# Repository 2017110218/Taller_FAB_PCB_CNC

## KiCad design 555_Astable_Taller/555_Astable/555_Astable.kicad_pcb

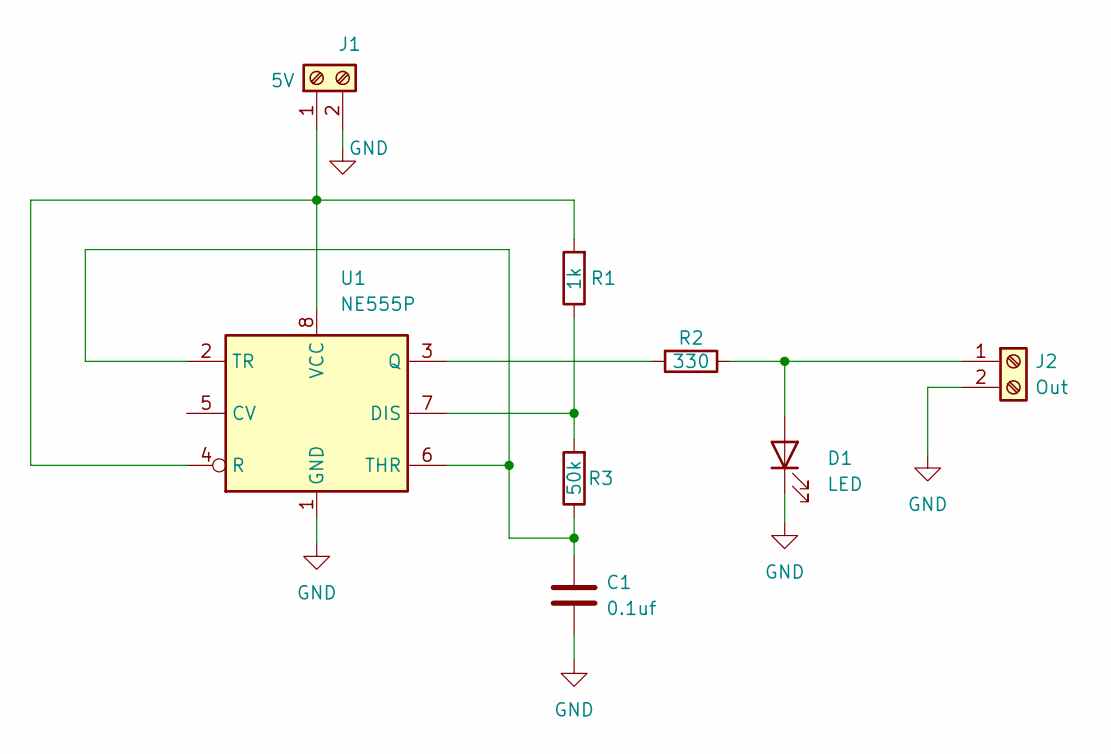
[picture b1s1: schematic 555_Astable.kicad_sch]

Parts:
C1: 0.1uf; C_Disc_D3.8mm_W2.6mm_P2.50mm
D1: LED; LED_D5.0mm
J1: 5V; TerminalBlock_Phoenix_MKDS-1,5-2_1x02_P5.00mm_Horizontal
J2: Out; TerminalBlock_Phoenix_MKDS-1,5-2_1x02_P5.00mm_Horizontal
R1: 1k; R_Axial_DIN0207_L6.3mm_D2.5mm_P7.62mm_Horizontal
R2: 330; R_Axial_DIN0207_L6.3mm_D2.5mm_P7.62mm_Horizontal
R3: 50k; R_Axial_DIN0207_L6.3mm_D2.5mm_P7.62mm_Horizontal
U1: NE555P; DIP-8_W7.62mm

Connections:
GND: C1.2, D1.1 (K), J1.2, J2.2, U1.1 (GND)
unnamed: D1.2 (A), J2.1, R2.1
unnamed: J1.1, R1.2, U1.4 (R), U1.8 (VCC)
unnamed: R1.1, R3.2, U1.7 (DIS)
unnamed: R2.2, U1.3 (Q)
unnamed: C1.1, R3.1, U1.2 (TR), U1.6 (THR)

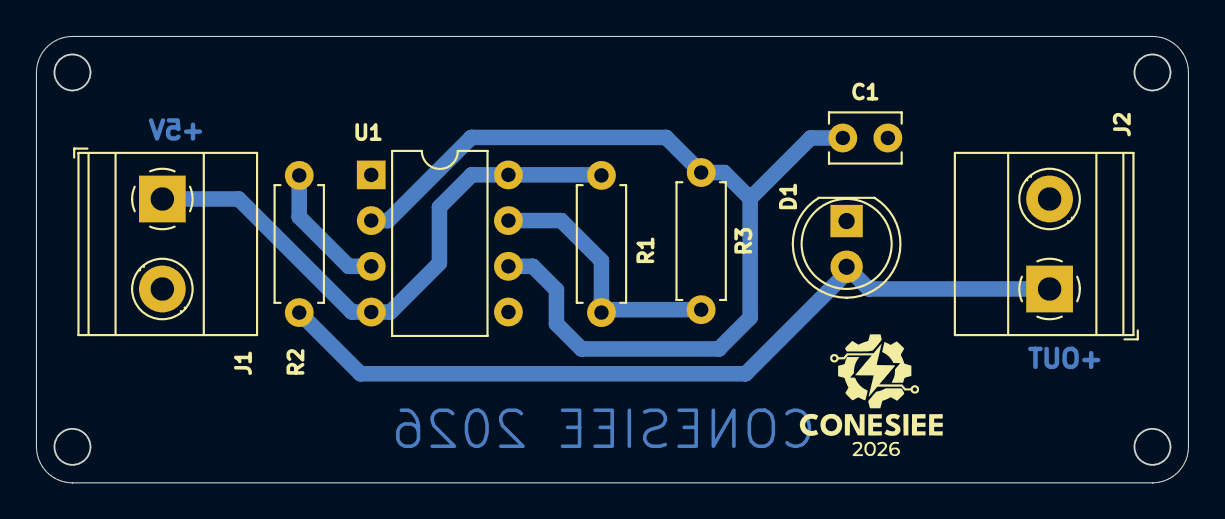
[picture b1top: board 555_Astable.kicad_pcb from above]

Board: 2 copper layers, 64.0 x 24.8 mm, 8 parts (0 on the bottom side), 6 nets.
